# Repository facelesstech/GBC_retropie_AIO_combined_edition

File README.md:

# GBC_retropie_AIO_combined_edition

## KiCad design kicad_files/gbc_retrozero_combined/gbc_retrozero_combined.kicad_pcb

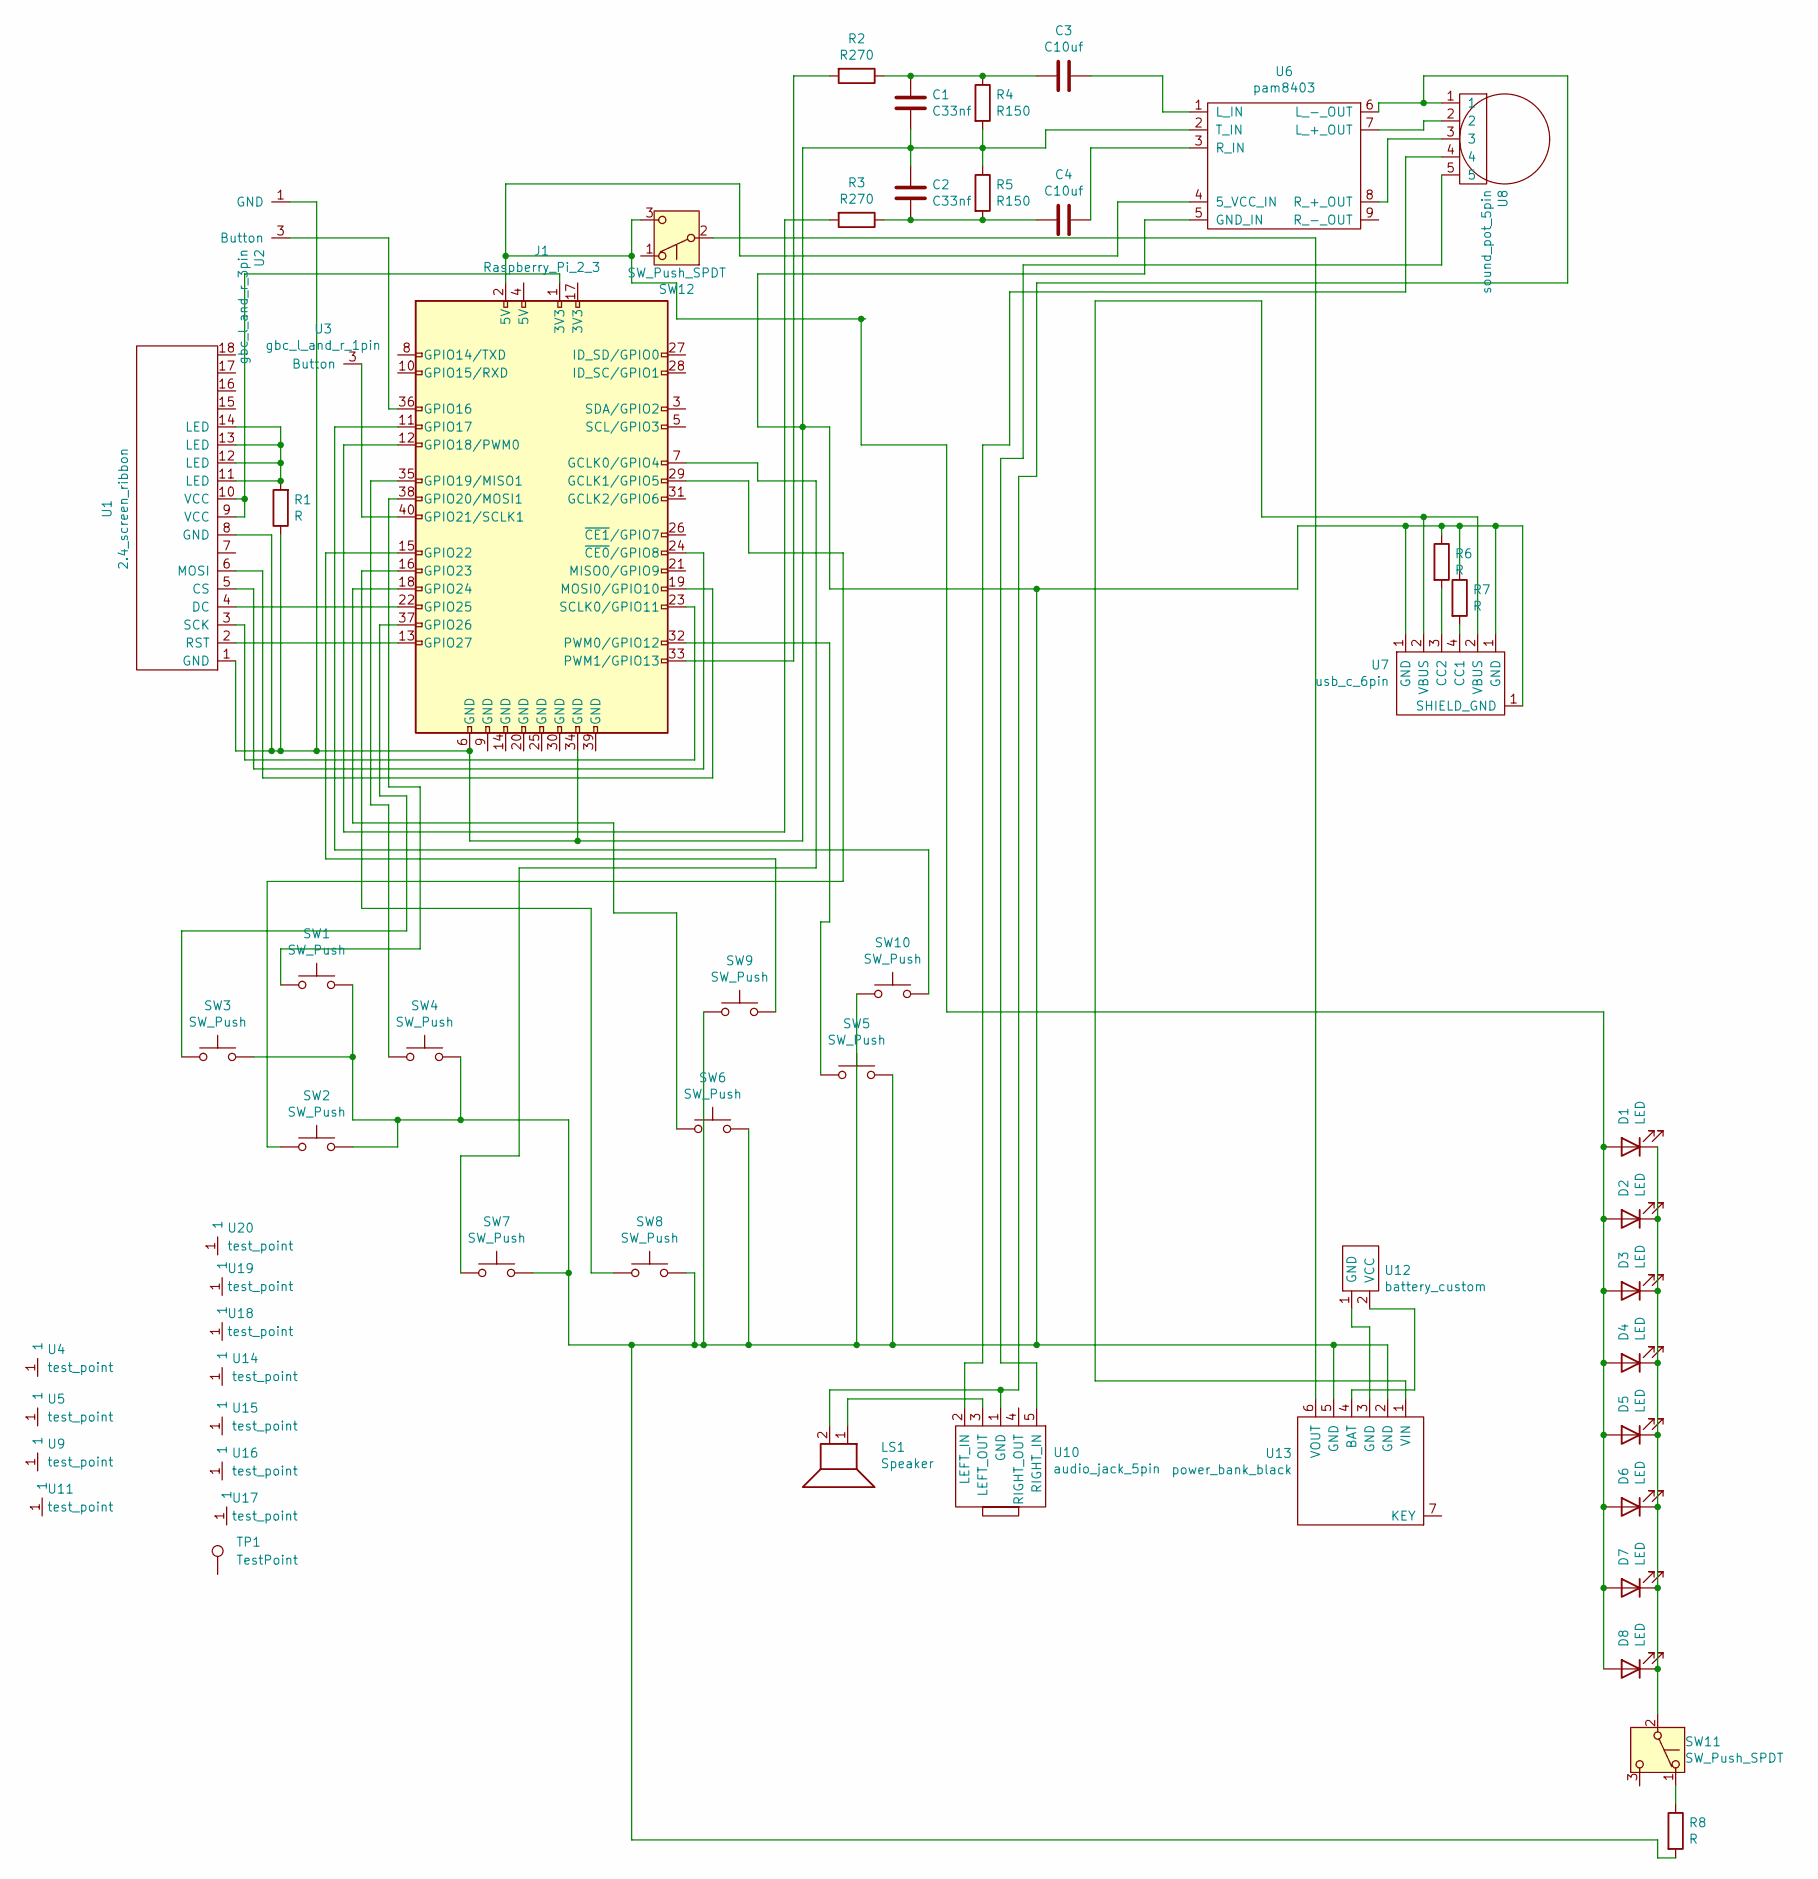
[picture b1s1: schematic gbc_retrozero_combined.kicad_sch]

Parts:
C1, C2: C33nf; C_1206_3216Metric_Pad1.33x1.80mm_HandSolder
C3, C4: C10uf; C_1206_3216Metric_Pad1.33x1.80mm_HandSolder
D1, D2, D3, D4, D5, D6, D7, D8: LED; LED_0603_1608Metric_Pad1.05x0.95mm_HandSolder
J1: Raspberry_Pi_2_3; raspberry_pi_gpio_SMD_outline_under_holes
LS1: Speaker; speaker_2pin
R1, R6, R7, R8: R; R_1206_3216Metric_Pad1.30x1.75mm_HandSolder
R2, R3: R270; R_1206_3216Metric_Pad1.30x1.75mm_HandSolder
R4, R5: R150; R_1206_3216Metric_Pad1.30x1.75mm_HandSolder
SW1, SW2, SW3, SW4, SW5, SW6: SW_Push; gbc_pad_buttons_small+clicky
SW7, SW8: SW_Push; gbc_start_button_plus_clicky
SW9, SW10: SW_Push; button_soft_touch_drill_hole_plus_clicky
SW11: SW_Push_SPDT; tiny_smd_slide_switch_adjustable
SW12: SW_Push_SPDT; 3_pin_switch_smd_side_mount
TP1: TestPoint; m3_hole_custom
U1: 2.4_screen_ribbon; 2.8_screen_ribbon_breakout
U2: gbc_l_and_r_3pin; GBC_L_and_R_3pin
U3: gbc_l_and_r_1pin; GBC_L_and_R_1pin
U4, U5, U9, U11, U14, U15, U16, U17, U18, U19, U20: test_point; GBC_mounting_holes
U6: pam8403; PAM8403_custom_smd
U7: usb_c_6pin; USB_C_6PIN_custom
U8: sound_pot_5pin; GBC_pot_custom
U10: audio_jack_5pin; 5_pin_3.5_jack
U12: battery_custom; vcc_gnd_2pin_custom
U13: power_bank_black; power_bank_black_smd

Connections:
unnamed: C1.1, C3.2, R2.1, R4.1
unnamed: C2.2, C4.2, R3.1, R5.2
unnamed: D1.2 (A), D2.2 (A), D3.2 (A), D4.2 (A), D5.2 (A), D6.2 (A), D7.2 (A), D8.2 (A), J1.2 (5V), SW12.3 (C), U6.4 (5_VCC_IN)
unnamed: D1.1 (K), D2.1 (K), D3.1 (K), D4.1 (K), D5.1 (K), D6.1 (K), D7.1 (K), D8.1 (K), SW11.2 (B)
unnamed: J1.1 (3V3), U1.9 (VCC), U1.10 (VCC)
unnamed: J1.7 (GCLK0/GPIO4), SW7.1
unnamed: J1.29 (GCLK1/GPIO5), SW2.1
unnamed: J1.36 (GPIO16), U2.3 (Button)
unnamed: J1.11 (GPIO17), SW10.2
unnamed: J1.12 (GPIO18/PWM0), R3.2
unnamed: J1.35 (GPIO19/MISO1), SW4.1
unnamed: J1.38 (GPIO20/MOSI1), SW1.1
unnamed: J1.40 (GPIO21/SCLK1), U3.3 (Button)
unnamed: J1.15 (GPIO22), SW9.2
unnamed: J1.16 (GPIO23), SW8.1
unnamed: J1.18 (GPIO24), SW6.1
unnamed: J1.22 (GPIO25), U1.4 (DC)
unnamed: J1.37 (GPIO26), SW3.1
unnamed: J1.13 (GPIO27), U1.2 (RST)
unnamed: J1.19 (MOSI0/GPIO10), U1.6 (MOSI)
unnamed: J1.32 (PWM0/GPIO12), SW5.1
unnamed: J1.33 (PWM1/GPIO13), R2.2
unnamed: J1.23 (SCLK0/GPIO11), U1.3 (SCK)
unnamed: J1.24 (~CE0/GPIO8), U1.5 (CS)
unnamed: R1.2, U1.11 (LED), U1.12 (LED), U1.13 (LED), U1.14 (LED)
unnamed: R8.1, SW11.1 (A)
unnamed: SW12.2 (B), U13.6 (VOUT)
unnamed: C1.2, C2.1, J1.6 (GND), J1.34 (GND), R1.1, R4.2, R5.1, R6.1, R7.1, R8.2, SW1.2, SW2.2, SW3.2, SW4.2, SW5.2, SW6.2, SW7.2, SW8.2, SW9.1, SW10.1, U1.1 (GND), U1.8 (GND), U2.1 (GND), U6.2 (T_IN), U6.5 (GND_IN), U7.1 (SHIELD_GND), U13.2 (GND), U13.5 (GND)
unnamed: U6.7 (L_+_OUT), U8.2
unnamed: C3.1, U6.1 (L_IN)
unnamed: U6.8 (R_+_OUT), U8.3
unnamed: C4.1, U6.3 (R_IN)
unnamed: R7.2, U7.4 (CC1)
unnamed: R6.2, U7.3 (CC2)
unnamed: LS1.2, U6.6 (L_-_OUT), U8.1, U10.1 (GND)
unnamed: U8.4, U10.2 (LEFT_IN)
unnamed: LS1.1, U10.3 (LEFT_OUT)
unnamed: U8.5, U10.5 (RIGHT_IN)
unnamed: U12.1 (GND), U13.3 (GND)
unnamed: U12.2 (VCC), U13.4 (BAT)
unnamed: U7.2 (VBUS), U13.1 (VIN)

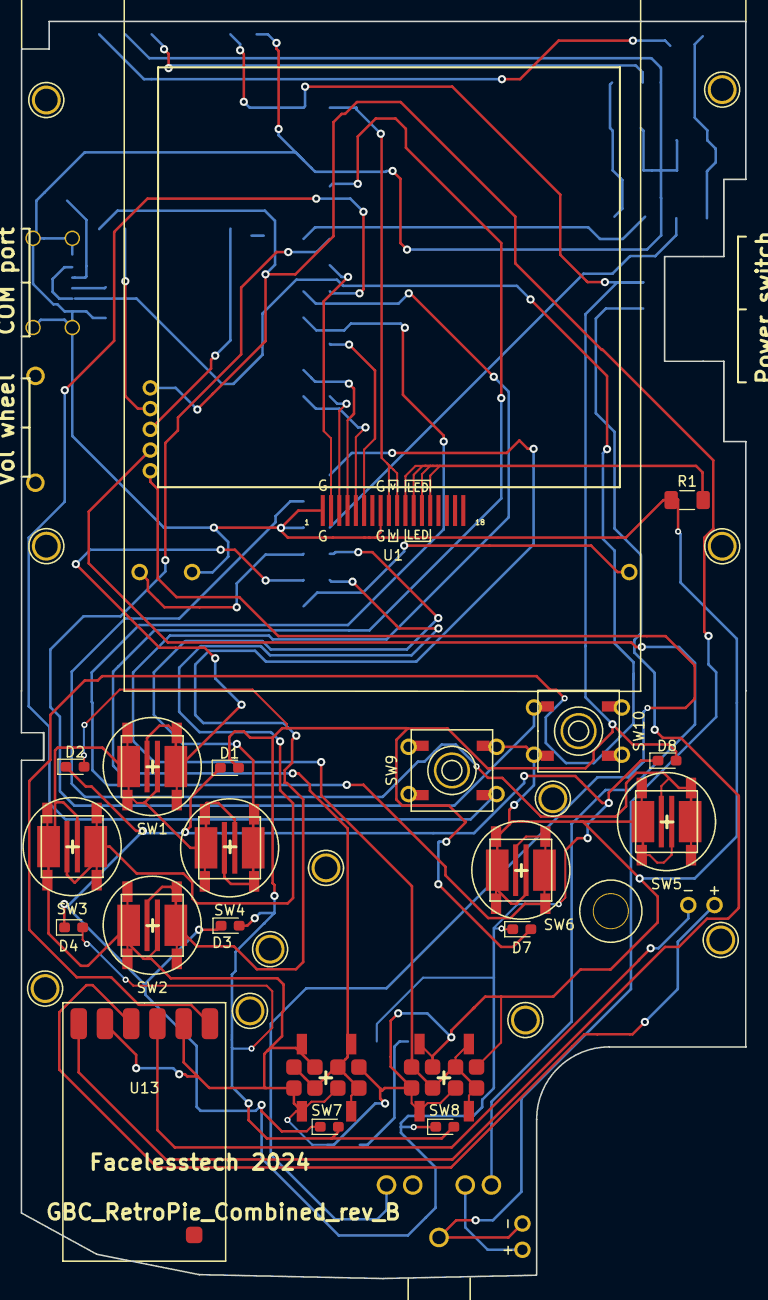
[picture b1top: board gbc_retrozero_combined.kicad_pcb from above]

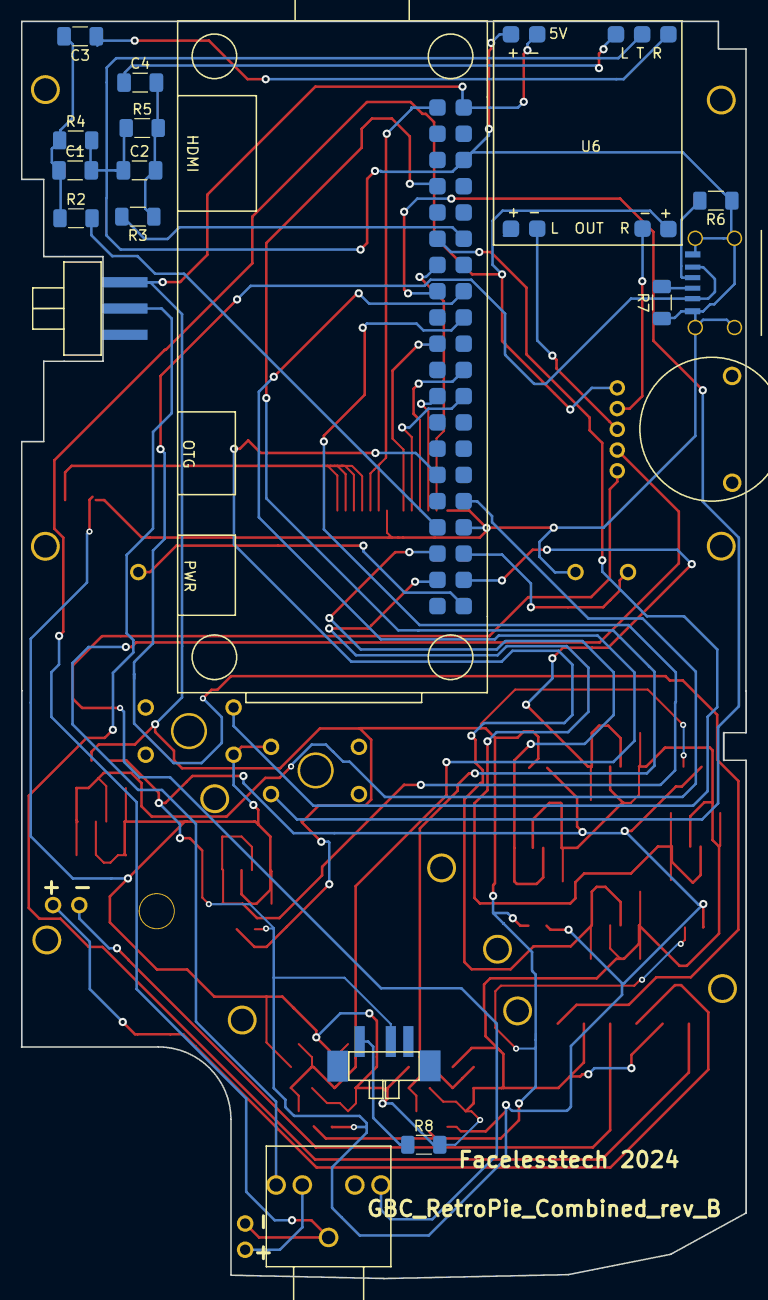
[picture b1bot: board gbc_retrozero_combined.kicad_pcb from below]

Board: 2 copper layers, 70.1 x 121.6 mm, 55 parts (18 on the bottom side), 41 nets.

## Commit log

2025-01-12 added license
2025-01-12 added 3d print files
2025-01-12 added kicad pcb files
